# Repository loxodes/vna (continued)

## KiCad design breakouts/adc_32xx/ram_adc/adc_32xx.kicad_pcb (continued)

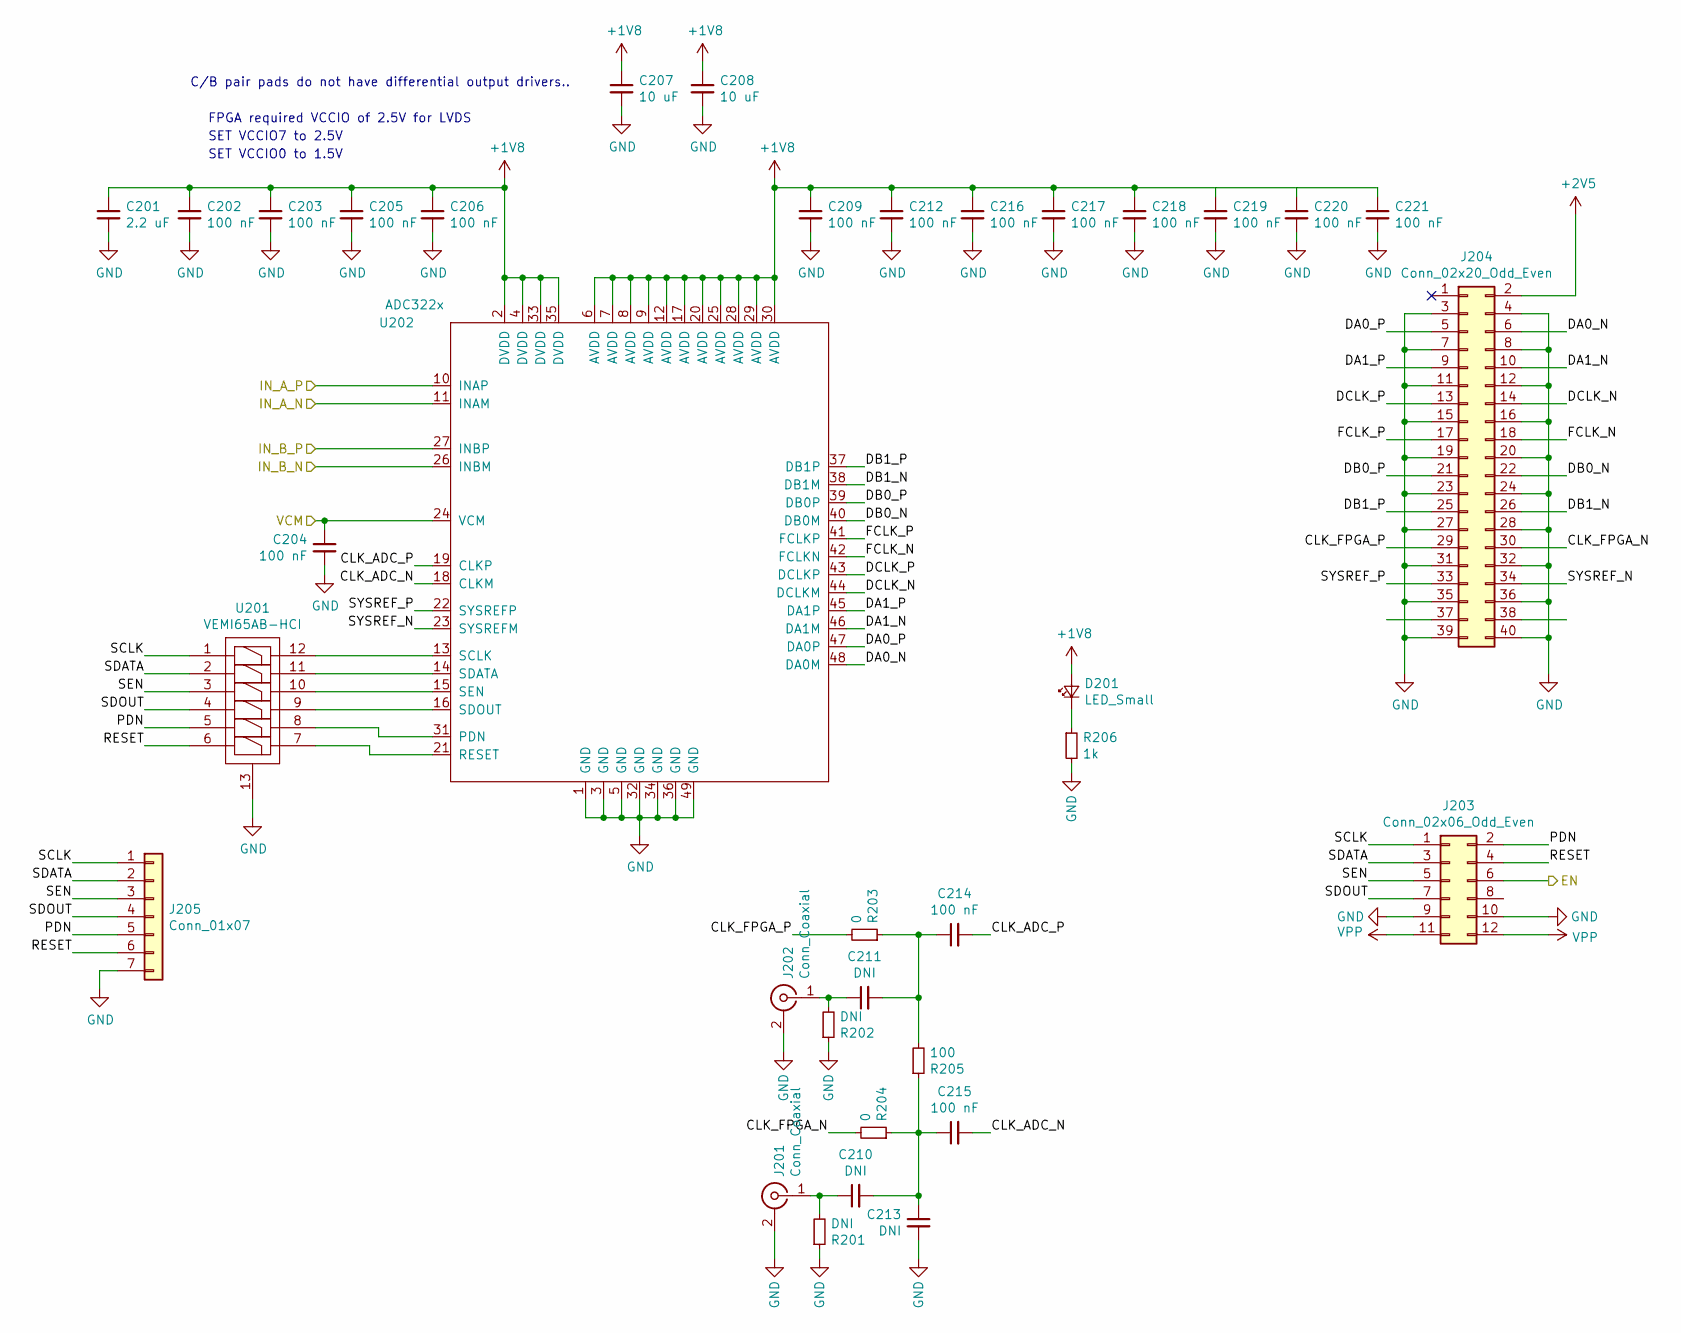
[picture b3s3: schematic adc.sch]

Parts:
C201: 2.2 uF; C_0603_1608Metric
C202, C203, C204, C205, C206, C209, C212, C214, C215, C216, C217, C218, C219, C220, C221: 100 nF; C_0402_1005Metric
C207, C208: 10 uF; C_0603_1608Metric
C210, C211, C213: DNI; C_0402_1005Metric
D201: LED_Small; LED_0603_1608Metric
J201, J202: Conn_Coaxial; 732512200_SMA
J203: Conn_02x06_Odd_Even; PinHeader_2x06_P2.54mm_Vertical
J204: Conn_02x20_Odd_Even; PinHeader_2x20_P2.54mm_Vertical
J205: Conn_01x07; PinSocket_1x07_P2.54mm_Vertical
R201, R202: DNI; R_0402_1005Metric
R203, R204: 0; R_0402_1005Metric
R205: 100; R_0402_1005Metric
R206: 1k; R_0402_1005Metric
U201: VEMI65AB-HCI; LLP2513-13L
U202: ADC322x; QFN-48-1EP_7x7mm_P0.5mm_EP5.6x5.6mm

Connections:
+1V8: C201.1, C202.1, C203.1, C205.1, C206.1, C207.1, C208.1, C209.1, C212.1, C216.1, C217.1, C218.1, C219.1, C220.1, C221.1, D201.2 (A), U202.2 (DVDD), U202.4 (DVDD), U202.6 (AVDD), U202.7 (AVDD), U202.8 (AVDD), U202.9 (AVDD), U202.12 (AVDD), U202.17 (AVDD), U202.20 (AVDD), U202.25 (AVDD), U202.28 (AVDD), U202.29 (AVDD), U202.30 (AVDD), U202.33 (DVDD), U202.35 (DVDD); also elsewhere on the board
+2V5: J204.2; also elsewhere on the board
/VCM: C204.1, U202.24 (VCM); also elsewhere on the board
/adc/CLK_ADC_N: C215.2, U202.18 (CLKM)
/adc/CLK_ADC_P: C214.2, U202.19 (CLKP)
/adc/CLK_FPGA_N: J204.30, R204.2
/adc/CLK_FPGA_P: J204.29, R203.2
/adc/DA0_N: J204.6, U202.48 (DA0M)
/adc/DA0_P: J204.5, U202.47 (DA0P)
/adc/DA1_N: J204.10, U202.46 (DA1M)
/adc/DA1_P: J204.9, U202.45 (DA1P)
/adc/DB0_N: J204.22, U202.40 (DB0M)
/adc/DB0_P: J204.21, U202.39 (DB0P)
/adc/DB1_N: J204.26, U202.38 (DB1M)
/adc/DB1_P: J204.25, U202.37 (DB1P)
/adc/DCLK_N: J204.14, U202.44 (DCLKM)
/adc/DCLK_P: J204.13, U202.43 (DCLKP)
/adc/EN: J203.6; also elsewhere on the board
/adc/FCLK_N: J204.18, U202.42 (FCLKN)
/adc/FCLK_P: J204.17, U202.41 (FCLKP)
/adc/IN_A_N: U202.11 (INAM); also elsewhere on the board
/adc/IN_A_P: U202.10 (INAP); also elsewhere on the board
/adc/IN_B_N: U202.26 (INBM); also elsewhere on the board
/adc/IN_B_P: U202.27 (INBP); also elsewhere on the board
/adc/PDN: J203.2, J205.5, U201.5
/adc/RESET: J203.4, J205.6, U201.6
/adc/SCLK: J203.1, J205.1, U201.1
/adc/SDATA: J203.3, J205.2, U201.2
/adc/SDOUT: J203.7, J205.4, U201.4
/adc/SEN: J203.5, J205.3, U201.3
/adc/SYSREF_N: J204.34, U202.23 (SYSREFM)
/adc/SYSREF_P: J204.33, U202.22 (SYSREFP)
GND: C201.2, C202.2, C203.2, C204.2, C205.2, C206.2, C207.2, C208.2, C209.2, C212.2, C213.2, C216.2, C217.2, C218.2, C219.2, C220.2, C221.2, J201.2 (Ext), J202.2 (Ext), J203.9, J203.10, J204.3, J204.4, J204.7, J204.8, J204.11, J204.12, J204.15, J204.16, J204.19, J204.20, J204.23, J204.24, J204.27, J204.28, J204.31, J204.32, J204.35, J204.36, J204.39, J204.40, J205.7, R201.1, R202.1, R206.2, U201.13, U202.1 (GND), U202.3 (GND), U202.5 (GND), U202.32 (GND), U202.34 (GND), U202.36 (GND), U202.49 (GND); also elsewhere on the board
unnamed: C210.1, J201.1 (In), R201.2
unnamed: C210.2, C213.1, C215.1, R204.1, R205.1
unnamed: C211.1, J202.1 (In), R202.2
unnamed: C211.2, C214.1, R203.1, R205.2
unnamed: D201.1 (K), R206.1
unnamed: U201.7, U202.21 (RESET)
unnamed: U201.8, U202.31 (PDN)
unnamed: U201.9, U202.16 (SDOUT)
unnamed: U201.10, U202.15 (SEN)
unnamed: U201.11, U202.14 (SDATA)
unnamed: U201.12, U202.13 (SCLK)
VPP: J203.11, J203.12; also elsewhere on the board

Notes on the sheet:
C/B pair pads do not have differential output drivers..
FPGA required VCCIO of 2.5V for LVDS
SET VCCIO7 to 2.5V
SET VCCIO0 to 1.5V

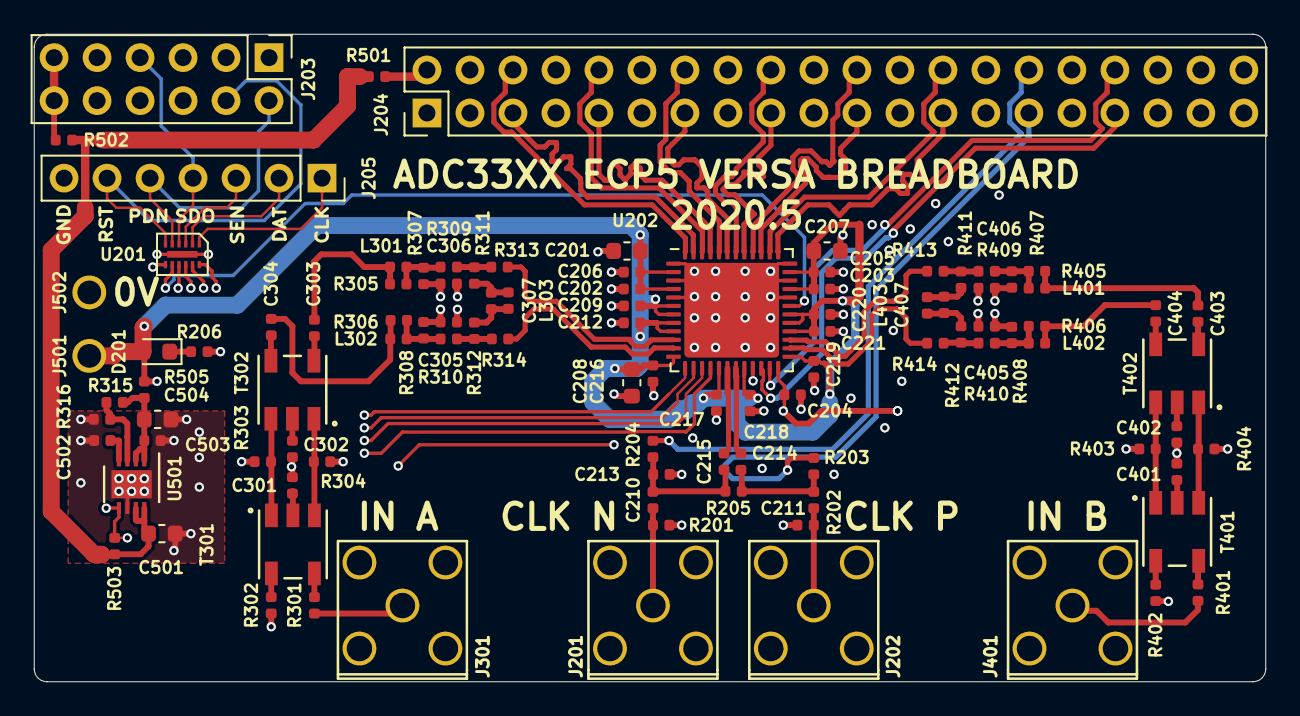
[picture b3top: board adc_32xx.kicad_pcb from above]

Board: 4 copper layers, 72.8 x 38.2 mm, 102 parts (0 on the bottom side), 83 nets.

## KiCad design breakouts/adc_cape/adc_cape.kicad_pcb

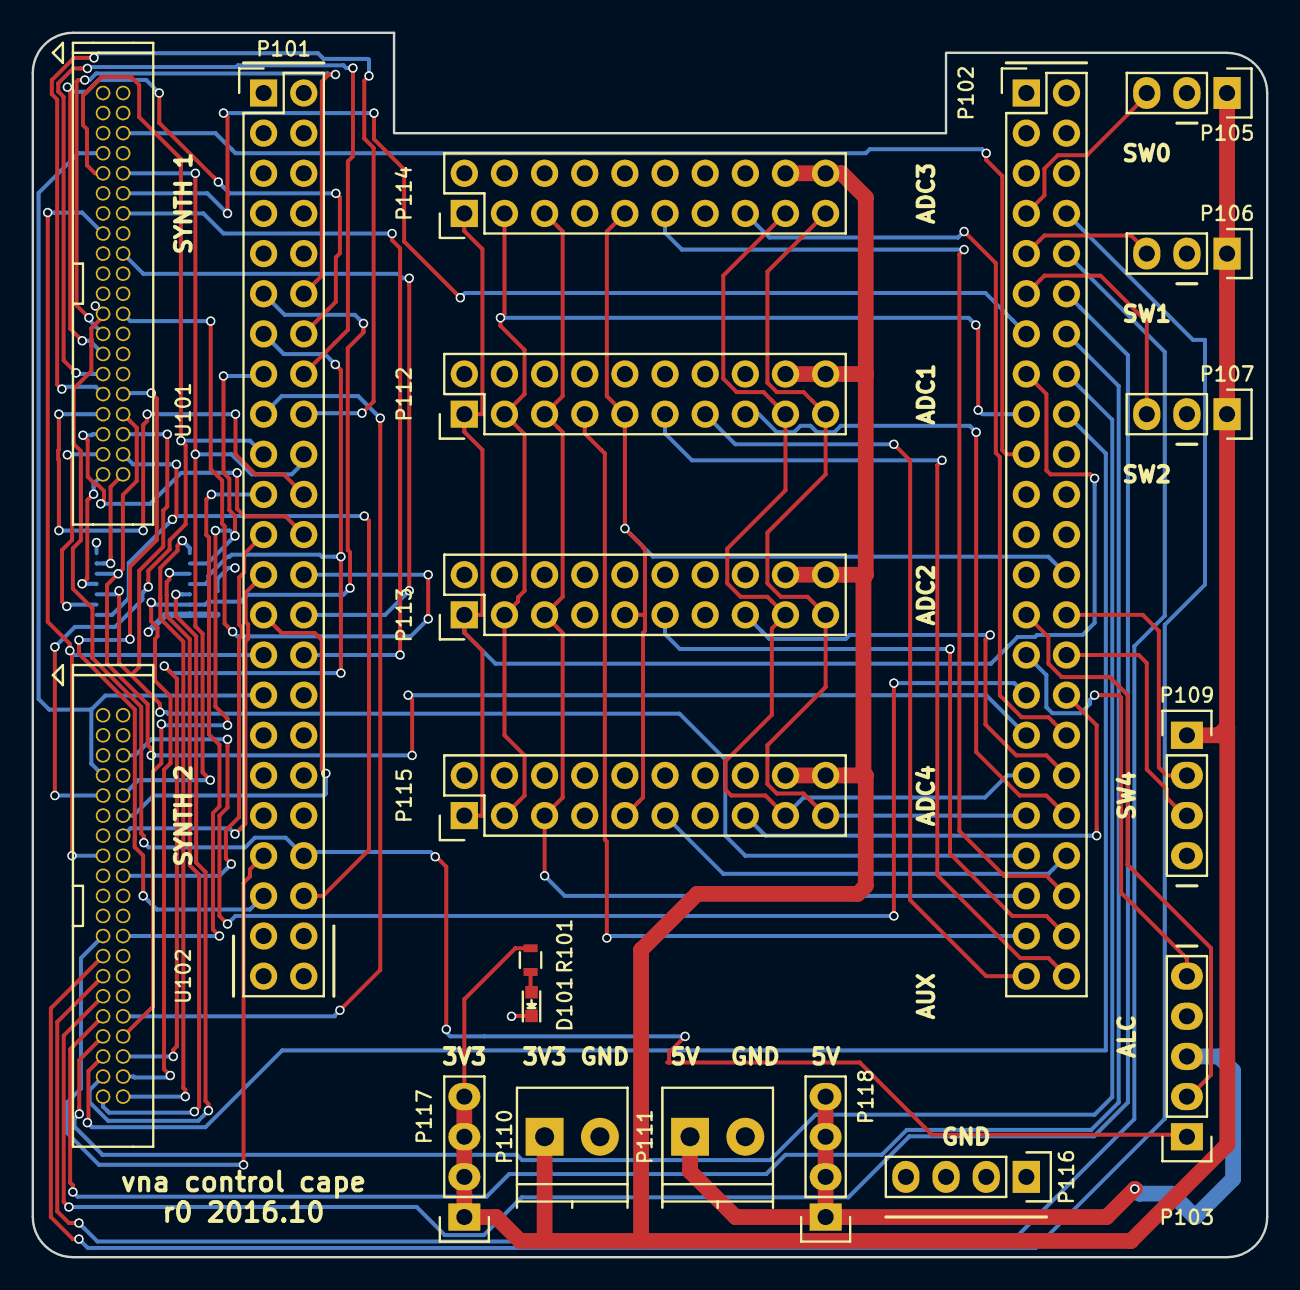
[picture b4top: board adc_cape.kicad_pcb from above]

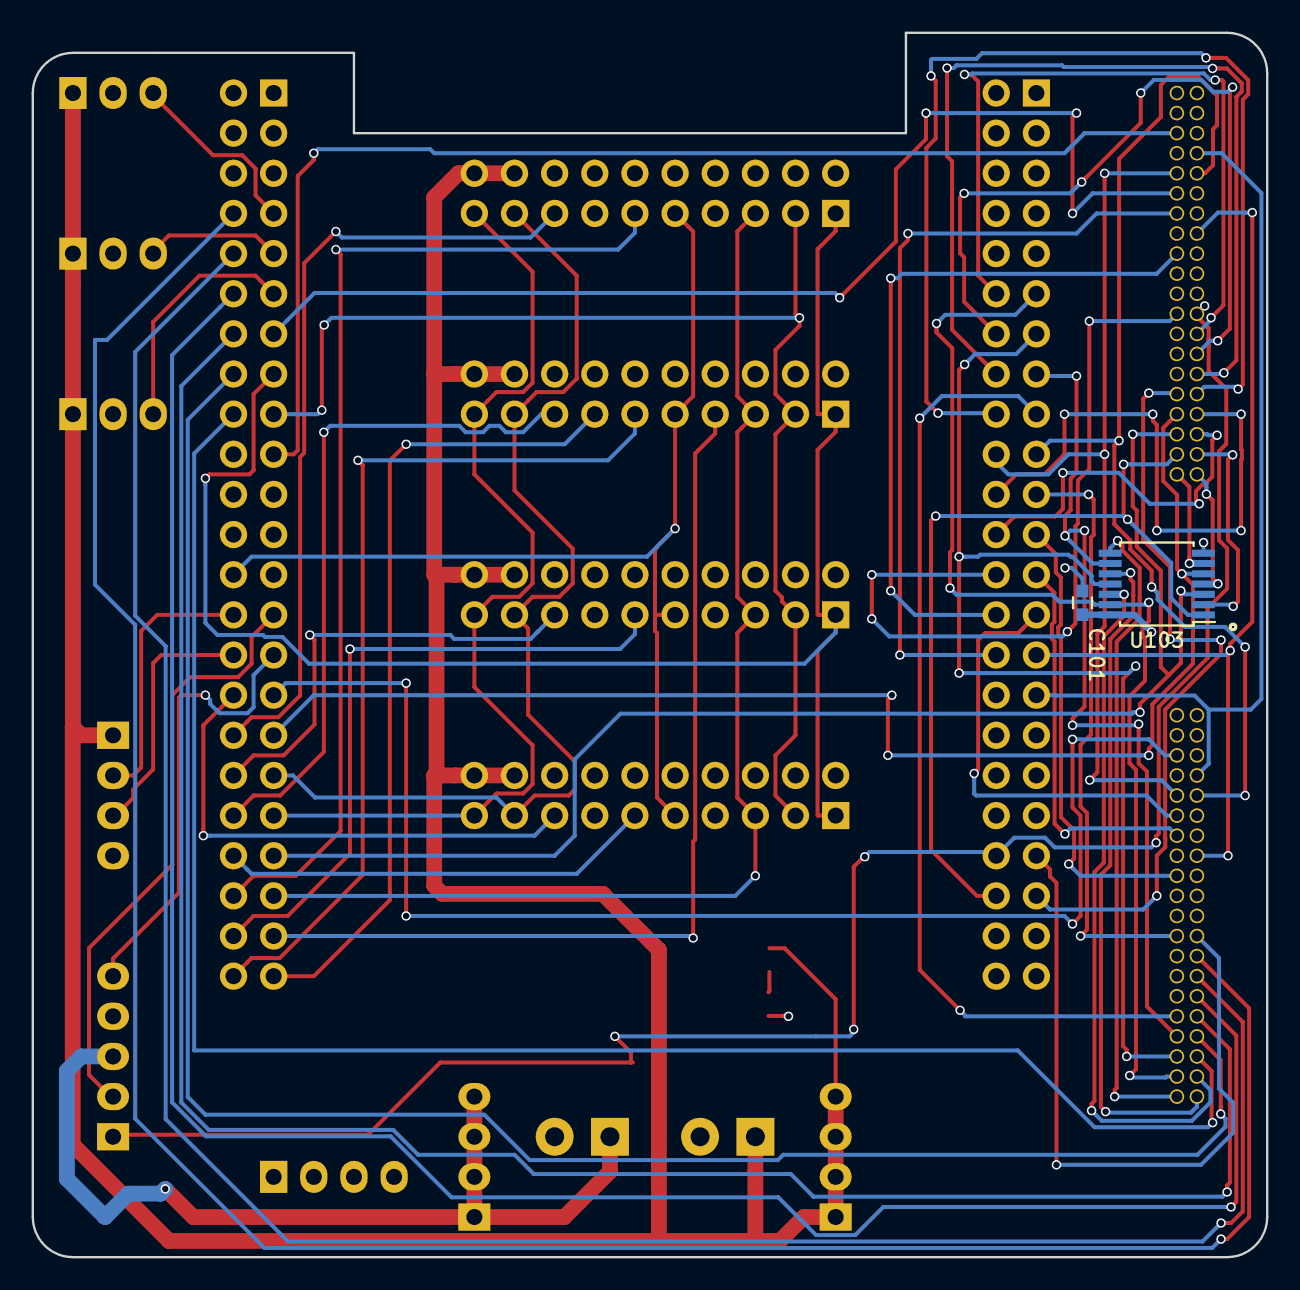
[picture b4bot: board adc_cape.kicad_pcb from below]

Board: 4 copper layers, 78.1 x 77.5 mm, 22 parts (2 on the bottom side), 69 nets.

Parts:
C101: 100 nF; C_0603
D101: LED; LED_0603
P101, P102: CONN_02X23; Pin_Header_Straight_2x23
P103: CONN_01X05; Pin_Header_Straight_1x05
P105, P106, P107: CONN_01X03; Pin_Header_Straight_1x03
P109, P116, P117, P118: CONN_01X04; Pin_Header_Straight_1x04
P110, P111: CONN_01X02; TerminalBlock_Pheonix_PT-3.5mm_2pol
P112, P113, P114, P115: CONN_02X10; Pin_Header_Straight_2x10
R101: 10k; R_0603
U101, U102: boosterpack_ti; 3221-40-0100-00_conn40
U103: 74HC04_FULL; TSSOP-14_4.4x5mm_Pitch0.65mm

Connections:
+3V3: C101.1, P105.1, P106.1, P107.1, P109.1, P110.1, P112.18, P112.20, P113.18, P113.20, P114.18, P114.20, P115.18, P115.20, P117.1, P117.2, P117.3, P117.4, R101.1, U103.14
+5V: P103.3, P111.1, P118.1, P118.2, P118.3, P118.4
/ALC_SW_1_1: P102.27, P103.2
/ALC_SW_1_2: P102.29, P103.5
/ATT_1_1: P101.24, U101.35
/ATT_1_2: P102.18, U102.35
/ATT_2_1: P101.22, U101.33
/ATT_2_2: P102.16, U102.33
/ATT_3_1: P101.18, U101.31
/ATT_3_2: P102.14, U102.31
/ATT_4_1: P101.16, U101.29
/ATT_4_2: P102.12, U102.29
/ATT_5_1: P101.14, U101.27
/ATT_5_2: P102.10, U102.27
/ATT_6_1: P101.12, U101.25
/ATT_6_2: P102.8, U102.25
/CLKOUT_ADC1: P102.45, P112.13
/DOUTA_ADC1: P102.46, P112.11
/DOUTA_ADC2: P102.44, P113.11
/DOUTA_ADC3: P102.42, P114.11
/DOUTA_ADC4: P102.40, P115.11
/DOUTB: P102.26, P112.9, P113.9, P114.9, P115.9
/FILTA_1: P101.42, U101.38, U103.1
/FILTA_2: P101.11, U102.38, U103.13
/FILTB_1: P102.39, U101.36, U103.3
/FILTB_2: P101.13, U102.36, U103.11
/FILTC_1: P102.33, U101.34, U103.5
/FILTC_2: P101.15, U102.34, U103.9
/FILT~A~_1: U101.37, U103.2
/FILT~A~_2: U102.37, U103.12
/FILT~B~_1: U101.39, U103.4
/FILT~B~_2: U102.39, U103.10
/FILT~C~_1: U101.40, U103.6
/FILT~C~_2: U102.40, U103.8
/FS_ADC1: P102.43, P112.7
/LMXPOW_EN_1: P101.41, U101.32
/LMXPOW_EN_2: P101.17, U102.32
/LMX_CE_1: P101.28, U101.18
/LMX_CE_2: P101.23, U102.18
/LMX_CLK: P101.31, U101.7, U102.7
/LMX_DATA: P101.29, U101.15, U102.15
/LMX_LE_1: P101.30, U101.14
/LMX_LE_2: P101.25, U102.14
/LMX_LOCK_1: P102.13, U101.12
/LMX_LOCK_2: P101.27, U102.12
/MIX_EN: P102.15, P112.1, P113.1, P114.1, P115.1
/MIX_X2: P102.17, P112.3, P113.3, P114.3, P115.3
/PC: P102.37, P112.19, P113.19, P114.19, P115.19
/PD: P102.35, P112.17, P113.17, P114.17, P115.17
/PE_ADC1: P102.38, P112.15
/PE_ADC2: P102.36, P113.15
/PE_ADC3: P102.34, P114.15
/PE_ADC4: P102.32, P115.15
/POWERDET_1: P101.40, P103.1, U101.23
/POWERDET_2: P101.39, U102.23
/REF_OE_1: P101.26, U101.24
/REF_OE_2: P101.21, U102.24
/REF_SCL: P101.19, U101.9, U102.9
/REF_SDA: P101.20, U101.10, U102.10
/RFSW_1: P102.19, U101.6
/RFSW_2: P102.31, U102.6
/SW2_0: P102.7, P105.3
/SW2_1: P102.9, P106.3
/SW2_2: P102.11, P107.3
/SW4_0_0: P102.28, P109.2
/SW4_0_1: P102.30, P109.3
/SYNCB: P102.41, P112.5, P113.5, P114.5, P115.5
GND: C101.2, D101.1, P101.1, P101.2, P101.34, P101.43, P101.44, P101.45, P101.46, P102.1, P102.2, P103.4, P105.2, P106.2, P107.2, P109.4, P110.2, P111.2, P112.2, P112.4, P112.6, P112.8, P112.10, P112.12, P112.14, P112.16, P113.2, P113.4, P113.6, P113.8, P113.10, P113.12, P113.14, P113.16, P114.2, P114.4, P114.6, P114.8, P114.10, P114.12, P114.14, P114.16, P115.2, P115.4, P115.6, P115.8, P115.10, P115.12, P115.14, P115.16, P116.1, P116.2, P116.3, P116.4, U101.20, U101.22, U102.20, U102.22, U103.7
unnamed: D101.2, R101.2

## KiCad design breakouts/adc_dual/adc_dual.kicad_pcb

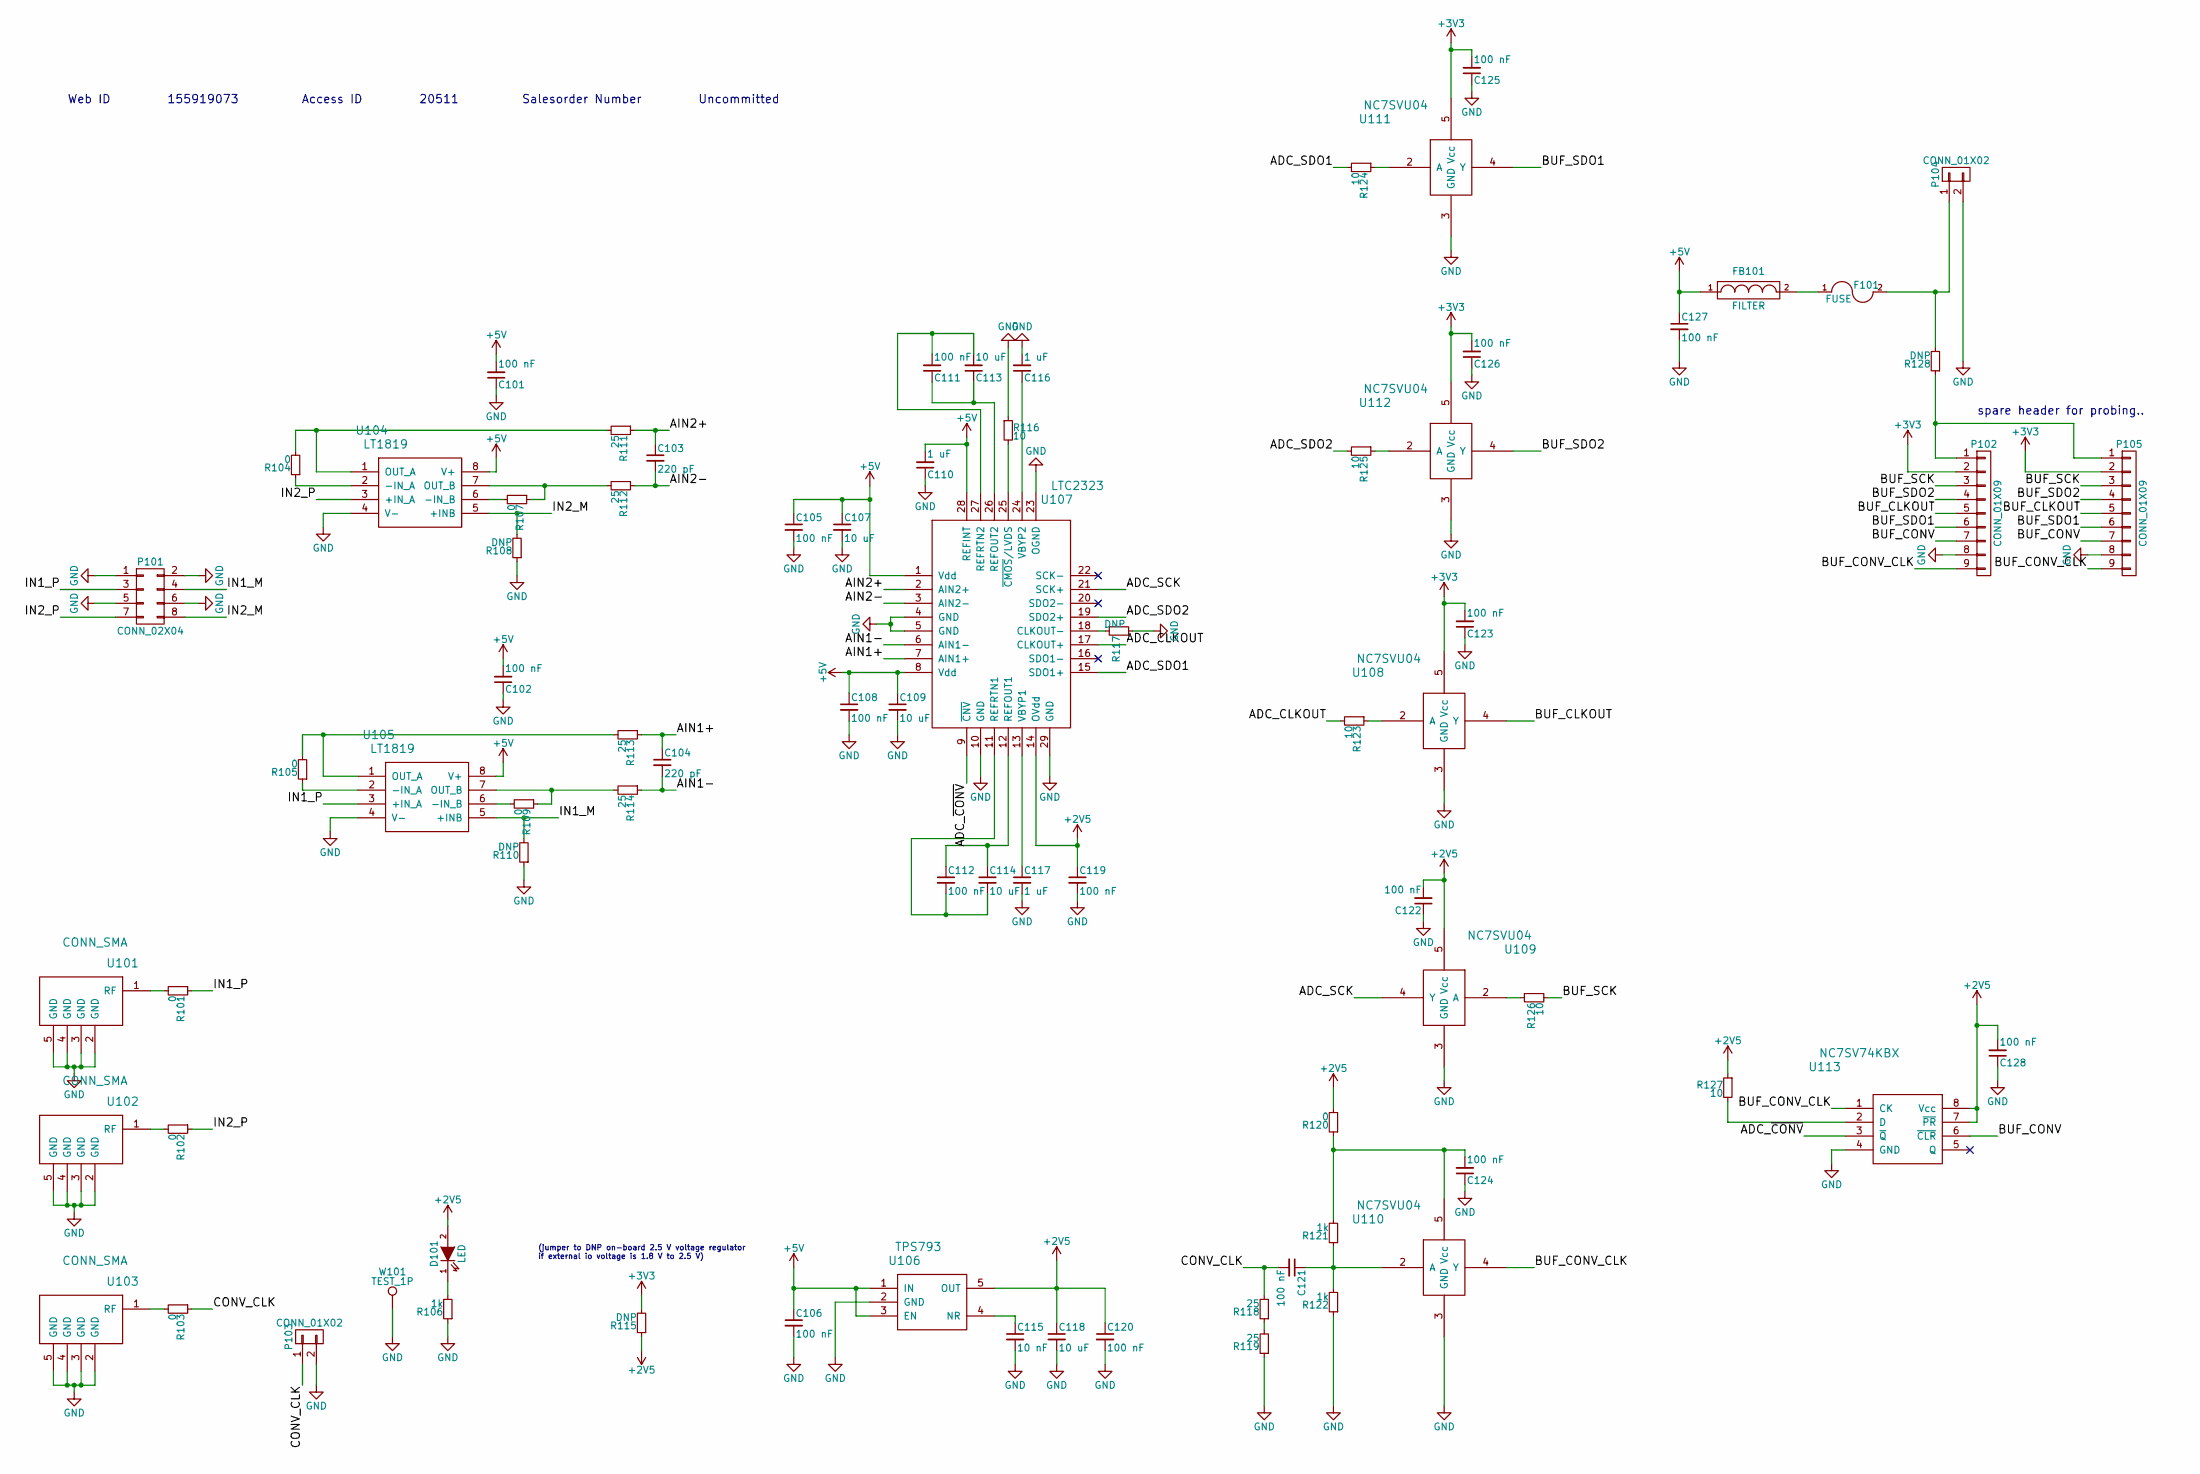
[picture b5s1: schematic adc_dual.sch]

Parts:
C101, C102, C105, C106, C108, C111, C112, C119, C120, C121, C122, C123, C124, C125, C126, C127, C128: 100 nF; C_0402
C103, C104: 220 pF; C_0402
C107, C109, C113, C114, C118: 10 uF; C_0603
C110, C116, C117: 1 uF; C_0402
C115: 10 nF; C_0603
D101: LED; LED_0603
F101: FUSE; R_1206
FB101: FILTER; R_0603
P101: CONN_02X04; Pin_Header_Straight_2x04
P102, P105: CONN_01X09; Pin_Header_Straight_1x09
P103: CONN_01X02; Pin_Header_Straight_2x01
P104: CONN_01X02; TerminalBlock_Pheonix_PT-3.5mm_2pol
R101, R102, R103, R104, R105, R107, R109, R120: 0; R_0402
R106, R121, R122: 1k; R_0402
R108, R110, R115, R117, R128: DNP; R_0402
R111, R112, R113, R114, R118, R119: 25; R_0402
R116, R123, R124, R125, R126, R127: 10; R_0402
U101, U102, U103: CONN_SMA; 732512200_SMA
U104, U105: LT1819; MSOP-8_3x3mm_Pitch0.65mm
U106: TPS793; SOT-23-5
U107: LTC2323; QFN-28-1EP_4x5mm_Pitch0.5mm
U108, U109, U110, U111, U112: NC7SVU04; SC-70-5
U113: NC7SV74KBX; US8
W101: TEST_1P; Pin_Header_Straight_1x01

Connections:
+2V5: C118.1, C119.1, C120.1, C122.2, C128.2, D101.2 (A), R115.1, R120.2, R127.1, U106.5 (OUT), U107.14 (OVdd), U109.5 (Vcc), U113.7 (~PR), U113.8 (Vcc)
+3V3: C123.2, C125.2, C126.2, P102.2, P105.2, R115.2, U108.5 (Vcc), U111.5 (Vcc), U112.5 (Vcc)
+5V: C101.2, C102.2, C105.1, C106.1, C107.1, C108.1, C109.1, C110.2, C127.1, FB101.1, U104.8 (V+), U105.8 (V+), U106.1 (IN), U106.3 (EN), U107.1 (Vdd), U107.8 (Vdd), U107.28 (REFINT)
/ADC_CLKOUT: R123.2, U107.17 (CLKOUT+)
/ADC_SCK: U107.21 (SCK+), U109.4 (Y)
/ADC_SDO1: R124.2, U107.15 (SDO1+)
/ADC_SDO2: R125.2, U107.19 (SDO2+)
/ADC_~CONV: U107.9 (~CNV), U113.3 (~Q)
/AIN1+: C104.1, R113.1, U107.7 (AIN1+)
/AIN1-: C104.2, R114.1, U107.6 (AIN1-)
/AIN2+: C103.1, R111.1, U107.2 (AIN2+)
/AIN2-: C103.2, R112.1, U107.3 (AIN2-)
/BUF_CLKOUT: P102.5, P105.5, U108.4 (Y)
/BUF_CONV: P102.7, P105.7, U113.6 (~CLR)
/BUF_CONV_CLK: P102.9, P105.9, U110.4 (Y), U113.1 (CK)
/BUF_SCK: P102.3, P105.3, R126.2
/BUF_SDO1: P102.6, P105.6, U111.4 (Y)
/BUF_SDO2: P102.4, P105.4, U112.4 (Y)
/CONV_CLK: C121.2, P103.1, R103.1, R118.2
/IN1_M: P101.4, R110.2, U105.5 (+INB)
/IN1_P: P101.3, R101.1, U105.3 (+IN_A)
/IN2_M: P101.8, R108.2, U104.5 (+INB)
/IN2_P: P101.7, R102.1, U104.3 (+IN_A)
GND: C101.1, C102.1, C105.2, C106.2, C107.2, C108.2, C109.2, C110.1, C115.2, C116.2, C117.2, C118.2, C119.2, C120.2, C122.1, C123.1, C124.1, C125.1, C126.1, C127.2, C128.1, P101.1, P101.2, P101.5, P101.6, P102.8, P103.2, P104.2, P105.8, R106.1, R108.1, R110.1, R116.1, R117.2, R119.1, R122.1, U101.2 (GND), U101.3 (GND), U101.4 (GND), U101.5 (GND), U102.2 (GND), U102.3 (GND), U102.4 (GND), U102.5 (GND), U103.2 (GND), U103.3 (GND), U103.4 (GND), U103.5 (GND), U104.4 (V-), U105.4 (V-), U106.2 (GND), U107.4 (GND), U107.5 (GND), U107.10 (GND), U107.23 (OGND), U107.29 (GND), U108.3 (GND), U109.3 (GND), U110.3 (GND), U111.3 (GND), U112.3 (GND), U113.4 (GND), W101.1
unnamed: C111.1, C113.1, U107.26 (REFOUT2)
unnamed: C111.2, C113.2, U107.27 (REFRTN2)
unnamed: C112.1, C114.1, U107.12 (REFOUT1)
unnamed: C112.2, C114.2, U107.11 (REFRTN1)
unnamed: C115.1, U106.4 (NR)
unnamed: C116.1, U107.24 (VBYP2)
unnamed: C117.1, U107.13 (VBYP1)
unnamed: C121.1, R121.1, R122.2, U110.2 (A)
unnamed: C124.2, R120.1, R121.2, U110.5 (Vcc)
unnamed: D101.1 (K), R106.2
unnamed: F101.1, FB101.2
unnamed: F101.2, P104.1, R128.2
unnamed: P102.1, P105.1, R128.1
unnamed: R101.2, U101.1 (RF)
unnamed: R102.2, U102.1 (RF)
unnamed: R103.2, U103.1 (RF)
unnamed: R104.1, U104.2 (-IN_A)
unnamed: R104.2, R111.2, U104.1 (OUT_A)
unnamed: R105.1, U105.2 (-IN_A)
unnamed: R105.2, R113.2, U105.1 (OUT_A)
unnamed: R107.1, R112.2, U104.7 (OUT_B)
unnamed: R107.2, U104.6 (-IN_B)
unnamed: R109.1, R114.2, U105.7 (OUT_B)
unnamed: R109.2, U105.6 (-IN_B)
unnamed: R116.2, U107.25 (~CMOS~/LVDS)
unnamed: R117.1, U107.18 (CLKOUT-)
unnamed: R118.1, R119.2
unnamed: R123.1, U108.2 (A)
unnamed: R124.1, U111.2 (A)
unnamed: R125.1, U112.2 (A)
unnamed: R126.1, U109.2 (A)
unnamed: R127.2, U113.2 (D)

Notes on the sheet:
spare header for probing..
(jumper to DNP on-board 2.5 V voltage regulator if external io voltage is 1.8 V to 2.5 V)
Web ID 155919073 Access ID 20511 Salesorder Number Uncommitted

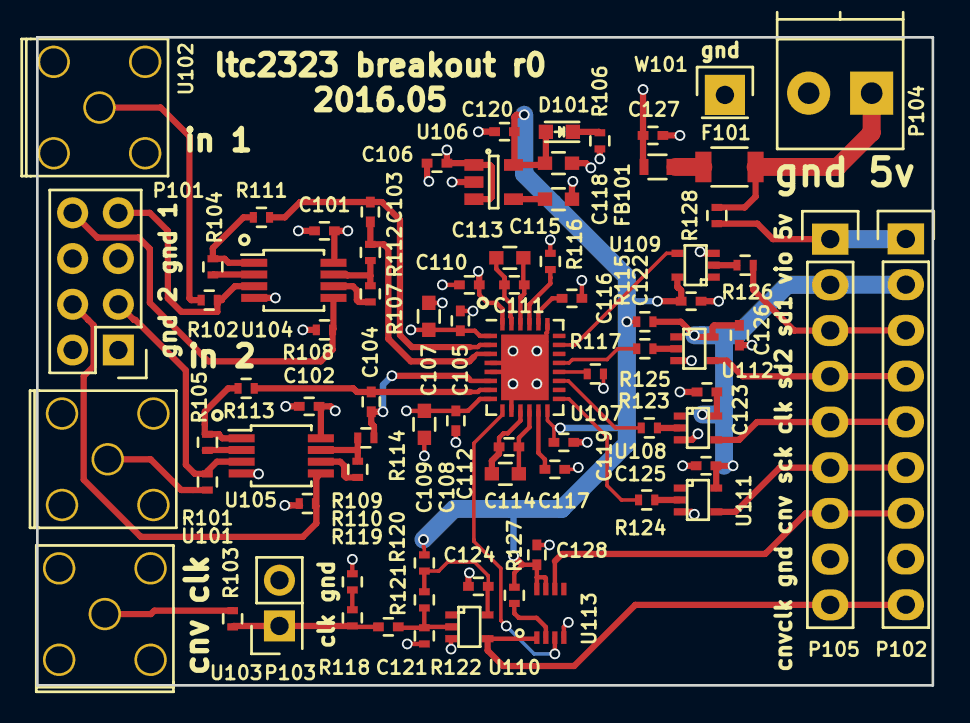
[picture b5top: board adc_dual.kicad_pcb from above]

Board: 4 copper layers, 49.8 x 36.0 mm, 78 parts (0 on the bottom side), 56 nets.

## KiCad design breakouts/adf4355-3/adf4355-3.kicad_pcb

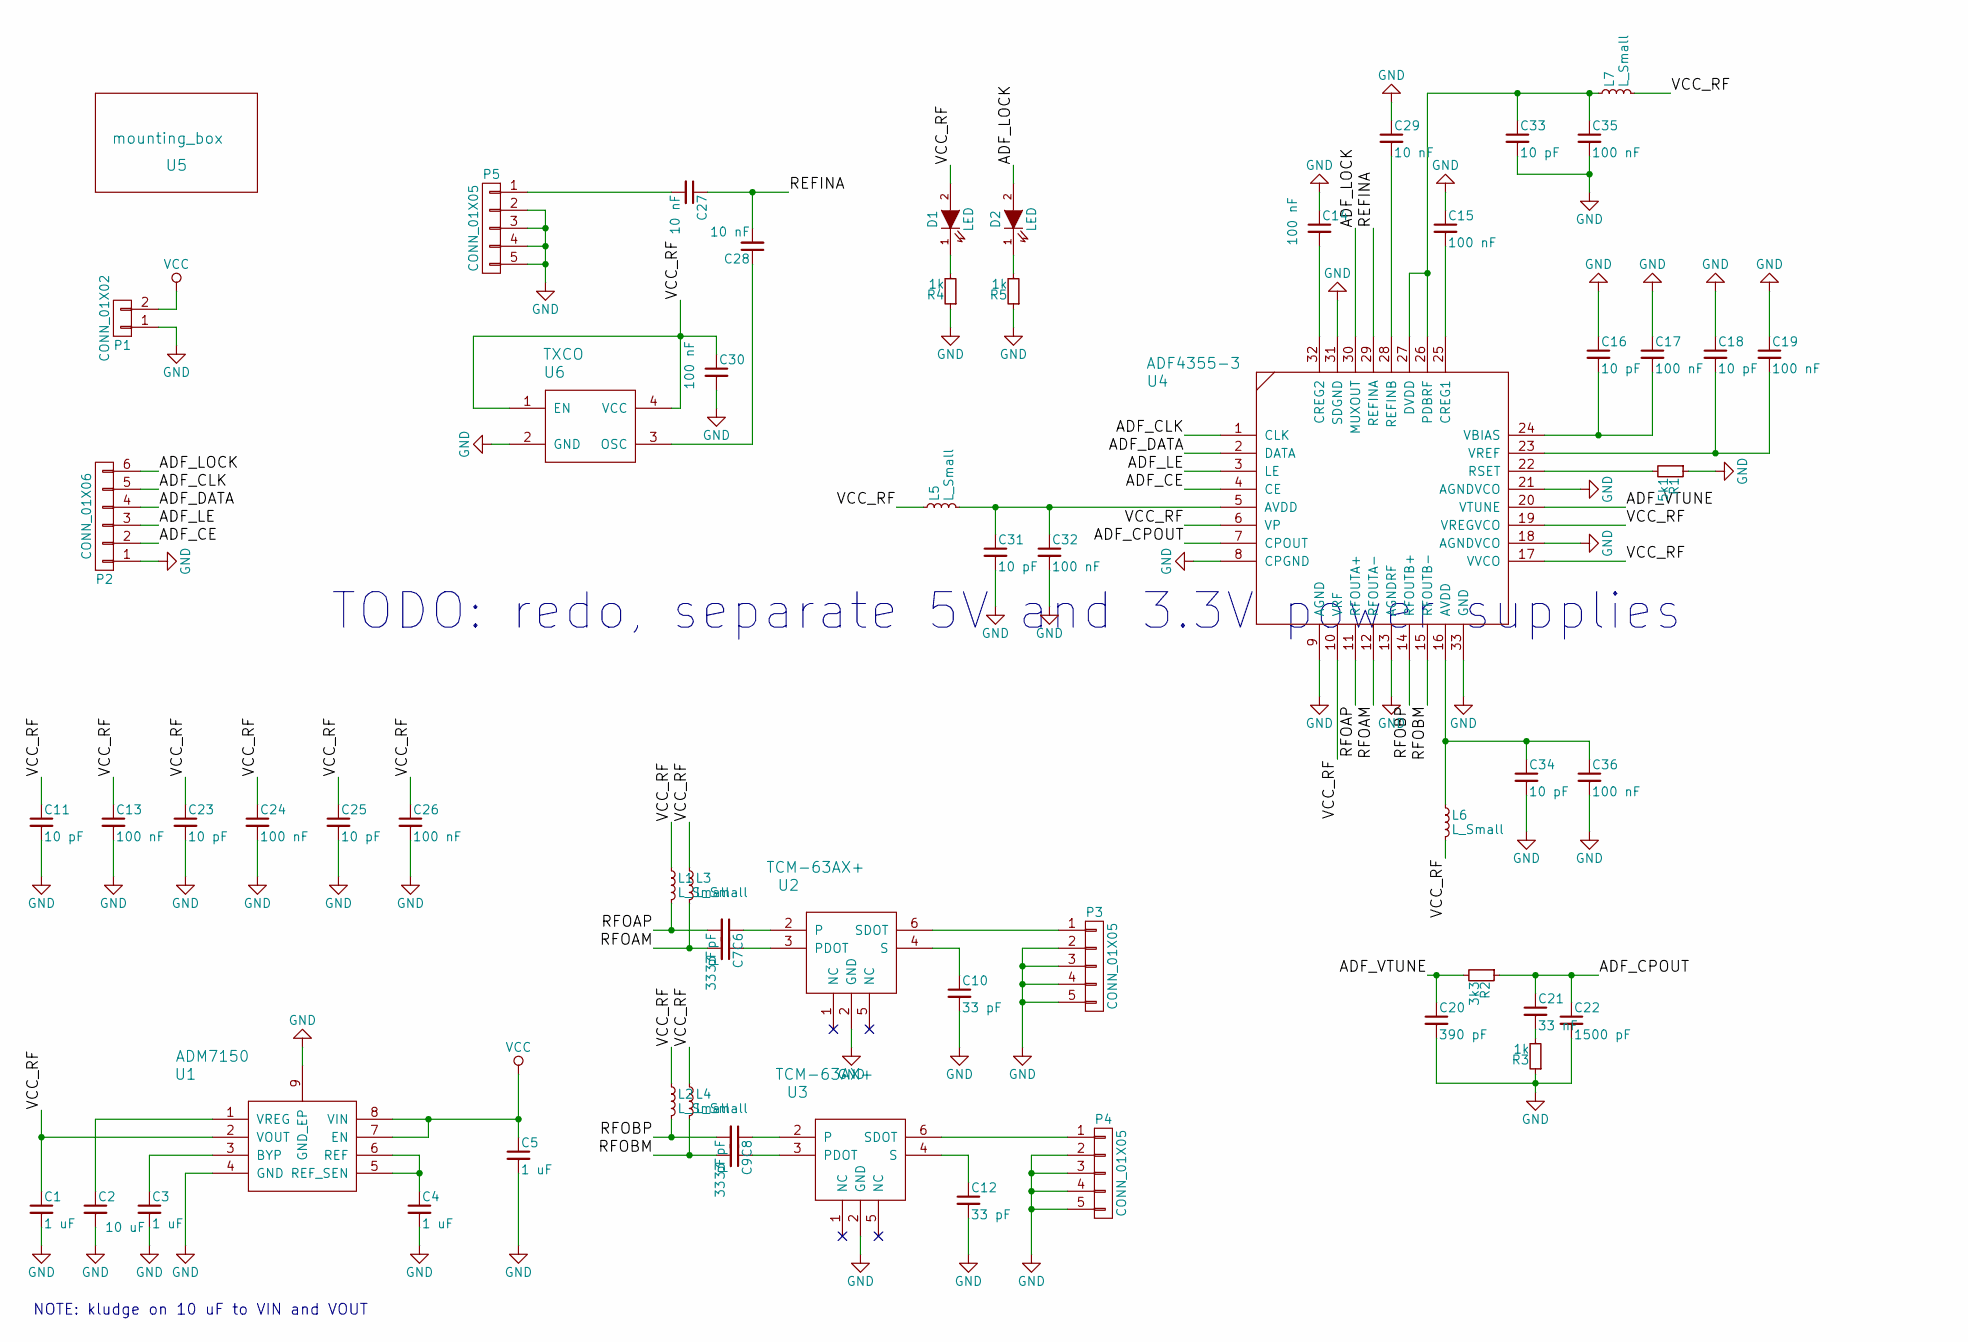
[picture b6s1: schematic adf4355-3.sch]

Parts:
C1, C3, C4, C5: 1 uF; C_0402
C2: 10 uF; C_0805
C6, C7, C8, C9, C10, C12: 33 pF; C_0402
C11, C16, C18, C23, C25, C31, C33, C34: 10 pF; C_0402
C13, C14, C15, C17, C19, C24, C26, C30, C32, C35, C36: 100 nF; C_0402
C20: 390 pF; C_0402
C21: 33 nF; C_0402
C22: 1500 pF; C_0402
C27, C28, C29: 10 nF; C_0402
D1, D2: LED; LED_0603
L1, L2, L3, L4, L5, L6, L7: L_Small; R_0402
P1: CONN_01X02; Pin_Header_Straight_1x02
P2: CONN_01X06; Pin_Header_Straight_1x06
P3, P4, P5: CONN_01X05; 732512200_SMA
R1: 5k1; R_0402
R2: 3k3; R_0402
R3, R4, R5: 1k; R_0402
U1: ADM7150; DFN-8-1EP_3x3mm_Pitch0.5mm
U2, U3: TCM-63AX+; TCM1-63AX+
U4: ADF4355-3; LFCSP_WQ_32
U5: mounting_box; POMONA_2400BOX
U6: TXCO; crystal_FA238-TSX3225

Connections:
/ADF_CE: P2.2, U4.4 (CE)
/ADF_CLK: P2.5, U4.1 (CLK)
/ADF_CPOUT: C21.1, C22.1, R2.1, U4.7 (CPOUT)
/ADF_DATA: P2.4, U4.2 (DATA)
/ADF_LE: P2.3, U4.3 (LE)
/ADF_LOCK: D2.2 (A), P2.6, U4.30 (MUXOUT)
/ADF_VTUNE: C20.1, R2.2, U4.20 (VTUNE)
/REFINA: C27.1, C28.2, U4.29 (REFINA)
/RFOAM: C7.2, L3.2, U4.12 (RFOUTA-)
/RFOAP: C6.2, L1.2, U4.11 (RFOUTA+)
/RFOBM: C9.2, L4.2, U4.15 (RFOUTB-)
/RFOBP: C8.2, L2.2, U4.14 (RFOUTB+)
/VCC_RF: C1.1, C11.1, C13.1, C23.1, C24.1, C25.1, C26.1, C30.1, D1.2 (A), L1.1, L2.1, L3.1, L4.1, L5.1, L6.2, L7.2, U1.2 (VOUT), U4.6 (VP), U4.10 (VRF), U4.17 (VVCO), U4.19 (VREGVCO), U6.1 (EN), U6.4 (VCC)
unnamed: C2.1, U1.1 (VREG)
unnamed: C3.1, U1.3 (BYP)
unnamed: C4.1, U1.5 (REF_SEN), U1.6 (REF)
unnamed: C7.1, U2.3 (PDOT)
unnamed: C9.1, U3.3 (PDOT)
unnamed: C10.1, U2.4 (S)
unnamed: C12.1, U3.4 (S)
unnamed: C14.2, U4.32 (CREG2)
unnamed: C15.2, U4.25 (CREG1)
unnamed: C16.2, C17.2, U4.24 (VBIAS)
unnamed: C18.2, C19.2, U4.23 (VREF)
unnamed: C21.2, R3.2
unnamed: C27.2, P5.1
unnamed: C28.1, U6.3 (OSC)
unnamed: C29.2, U4.28 (REFINB)
unnamed: C31.1, C32.1, L5.2, U4.5 (AVDD)
unnamed: C33.1, C35.1, L7.1, U4.26 (PDBRF), U4.27 (DVDD)
unnamed: C34.1, C36.1, L6.1, U4.16 (AVDD)
unnamed: D1.1 (K), R4.2
unnamed: D2.1 (K), R5.2
unnamed: P3.1, U2.6 (SDOT)
unnamed: P4.1, U3.6 (SDOT)
unnamed: R1.2, U4.22 (RSET)
VCC: C5.1, P1.2, U1.7 (EN), U1.8 (VIN)

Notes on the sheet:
NOTE: kludge on 10 uF to VIN and VOUT
TODO: redo, separate 5V and 3.3V power supplies

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
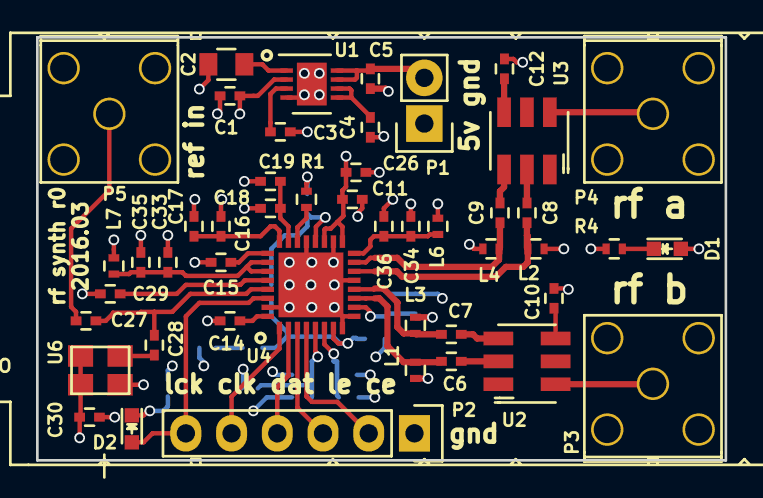
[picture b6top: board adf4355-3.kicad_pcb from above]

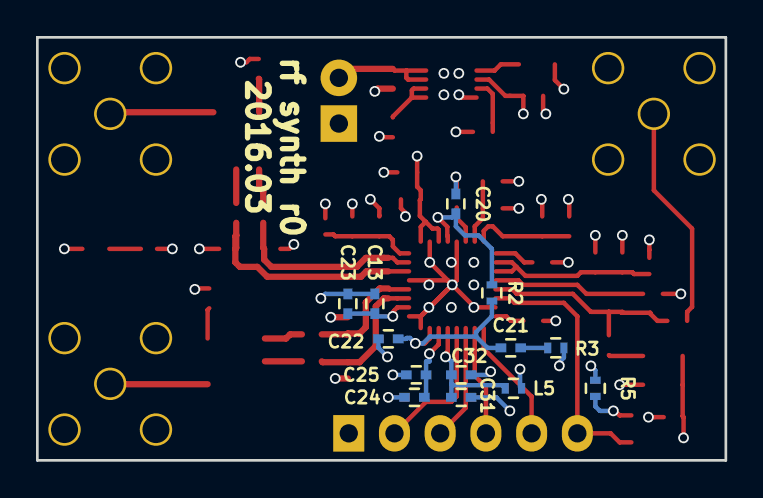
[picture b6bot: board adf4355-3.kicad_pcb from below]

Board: 4 copper layers, 38.2 x 23.5 mm, 61 parts (13 on the bottom side), 40 nets.
